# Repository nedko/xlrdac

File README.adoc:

[NOTE]
This is Work In Progress

Audio (XLR) Inputs and Outputs Open Source Hardware
project for use with libre software.

image:xlrdac-pcb-side.jpg["View of the line driver PCB", link="https://github.com/nedko/xlrdac/", width="100%"]

image:xlrdac-pcb.png["KiCAD screenshot of the line driver PCB", link="https://github.com/nedko/xlrdac/", width="100%"]

https://raw.githubusercontent.com/nedko/xlrdac/main/xlrdac-sch.pdf[Schematic], in PDF format.

Tools:

 * KiCAD - schematics and PCB design

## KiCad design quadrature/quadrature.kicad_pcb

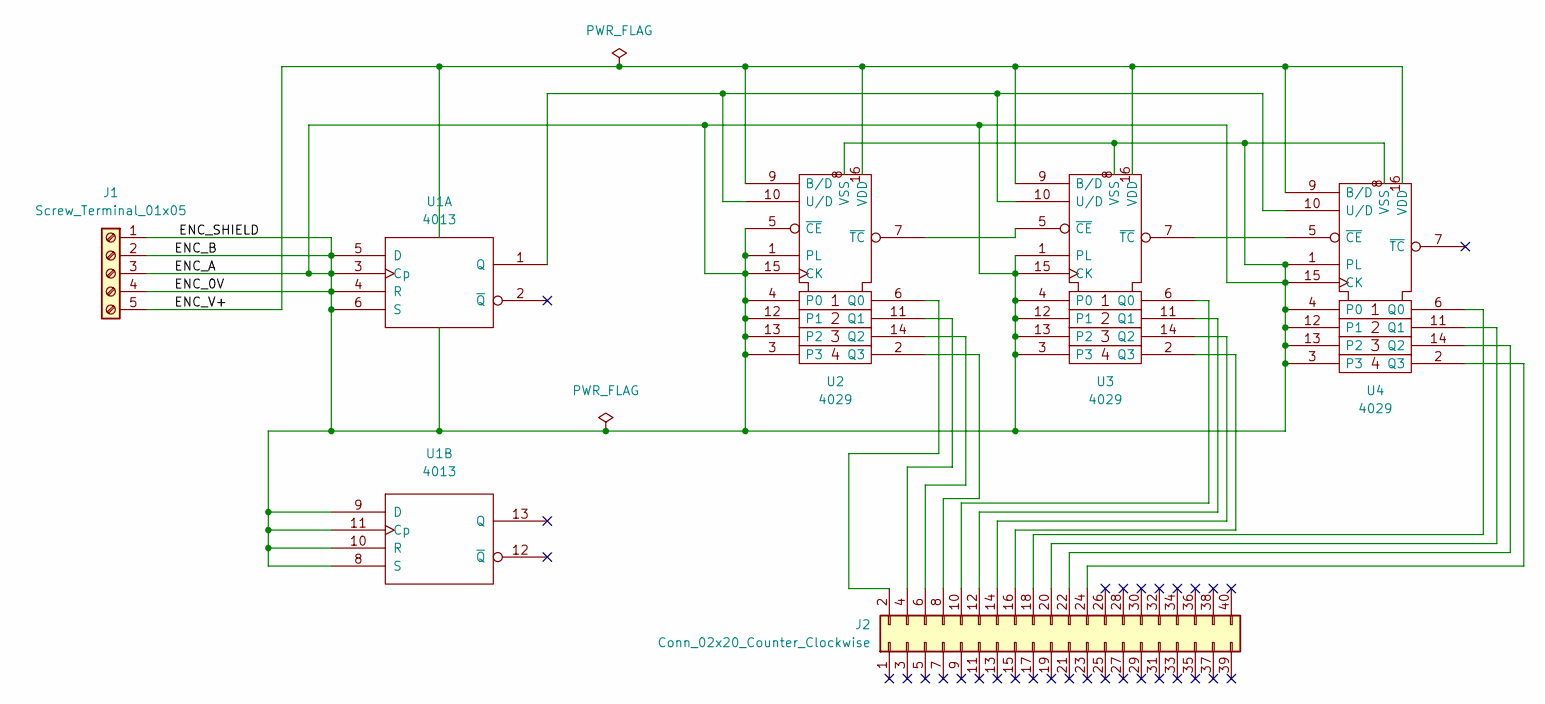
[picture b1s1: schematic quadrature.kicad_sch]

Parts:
J1: Screw_Terminal_01x05; TerminalBlock_bornier-5_P5.08mm
J2: Conn_02x20_Counter_Clockwise; IDC-Header_2x20_P2.54mm_Vertical
U1: 4013; DIP-14_W7.62mm_LongPads
U2, U3, U4: 4029; DIP-16_W7.62mm_LongPads

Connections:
unnamed: J2.2, U2.6 (Q0)
unnamed: J2.4, U2.11 (Q1)
unnamed: J2.6, U2.14 (Q2)
unnamed: J2.8, U2.2 (Q3)
unnamed: J2.10, U3.6 (Q0)
unnamed: J2.12, U3.11 (Q1)
unnamed: J2.14, U3.14 (Q2)
unnamed: J2.16, U3.2 (Q3)
unnamed: J2.18, U4.6 (Q0)
unnamed: J2.20, U4.11 (Q1)
unnamed: J2.22, U4.14 (Q2)
unnamed: J2.24, U4.2 (Q3)
unnamed: U1.1 (Q), U2.10 (U/D), U3.10 (U/D), U4.10 (U/D)
unnamed: U2.7 (~TC), U3.5 (~CE)
unnamed: U3.7 (~TC), U4.5 (~CE)
Vdd: J1.5, U1.14 (Vdd), U2.9 (B/D), U2.16 (VDD), U3.9 (B/D), U3.16 (VDD), U4.9 (B/D), U4.16 (VDD)
Vss: J1.1, J1.2, J1.3, J1.4, U1.3 (Cp), U1.4 (R), U1.5 (D), U1.6 (S), U1.7 (Vss), U1.8 (S), U1.9 (D), U1.10 (R), U1.11 (Cp), U2.1 (PL), U2.3, U2.4 (P0), U2.5 (~CE), U2.8 (VSS), U2.12 (P1), U2.13 (P2), U2.15 (CK), U3.1 (PL), U3.3, U3.4 (P0), U3.8 (VSS), U3.12 (P1), U3.13 (P2), U3.15 (CK), U4.1 (PL), U4.3, U4.4 (P0), U4.8 (VSS), U4.12 (P1), U4.13 (P2), U4.15 (CK)

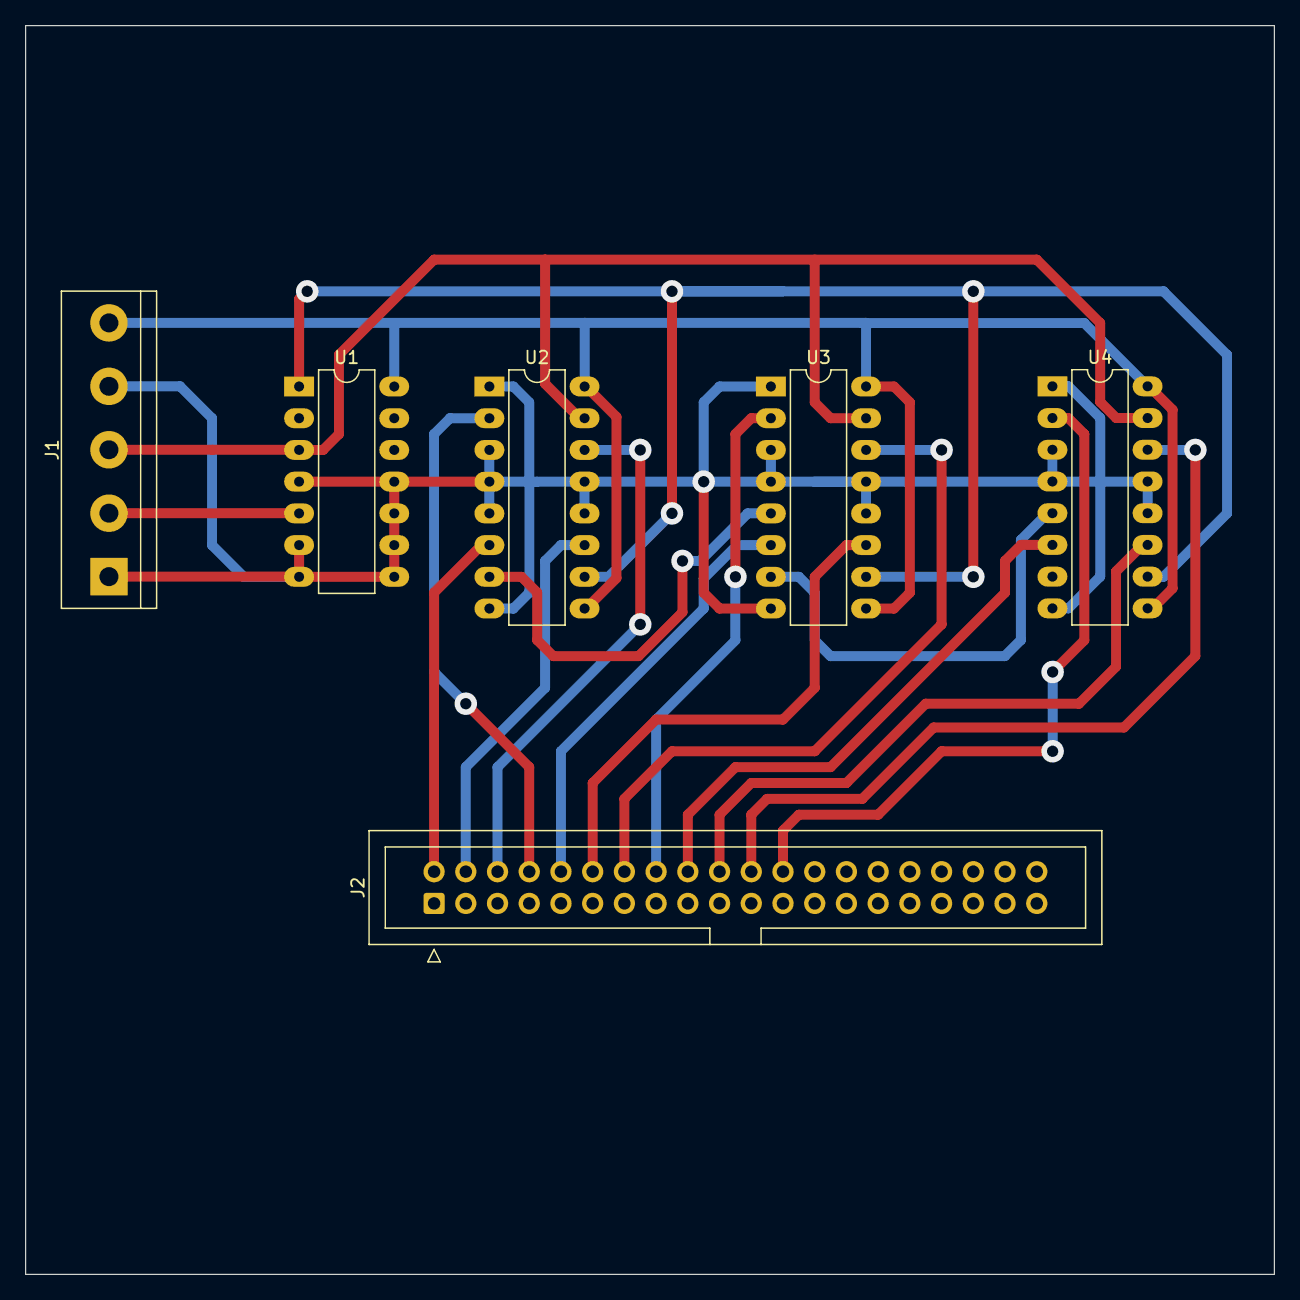
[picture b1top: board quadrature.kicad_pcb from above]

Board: 2 copper layers, 100.0 x 100.0 mm, 6 parts (0 on the bottom side), 17 nets.

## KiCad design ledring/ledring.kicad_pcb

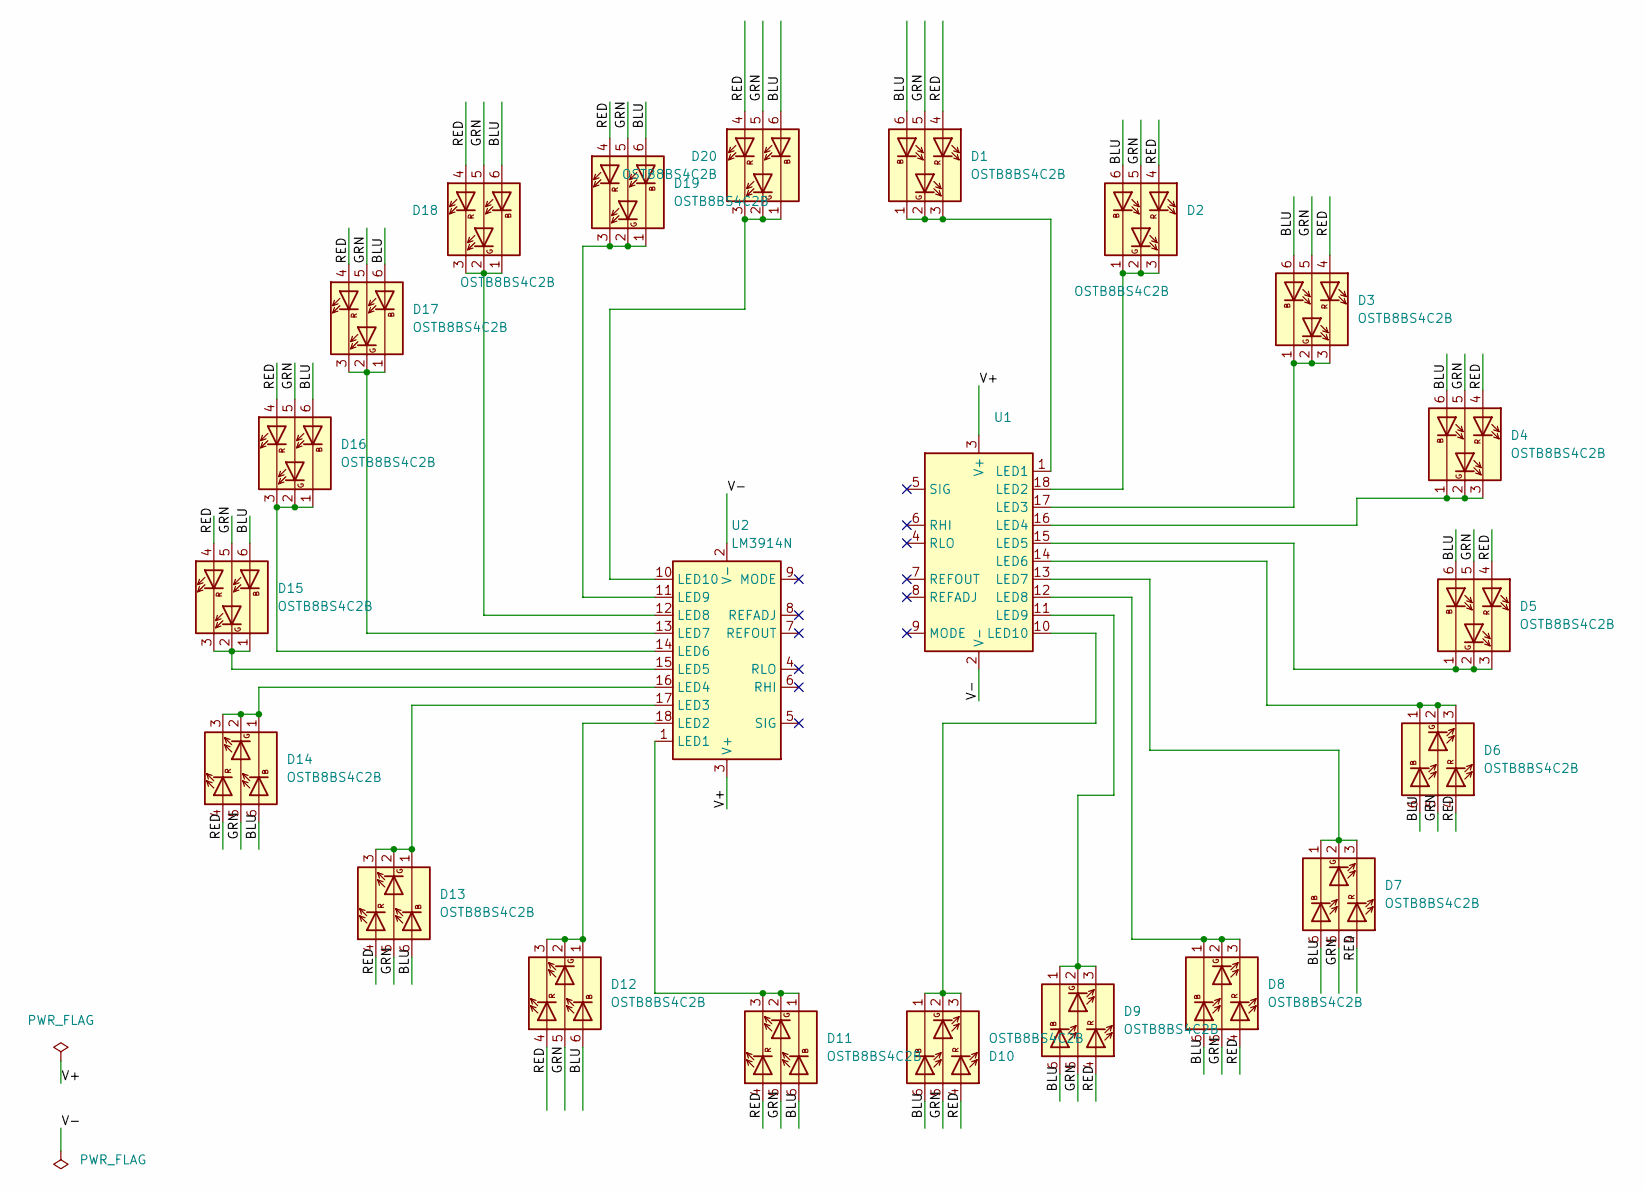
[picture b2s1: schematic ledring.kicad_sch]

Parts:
D1, D2, D3, D4, D5, D6, D7, D8, D9, D10, D11, D12, D13, D14, D15, D16, D17, D18, D19, D20: OSTB8BS4C2B; LED_Avago_PLCC6_3x2.8mm
U1: (no value)
U2: LM3914N; DIP-18_W7.62mm_LongPads

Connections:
/BLU: D1.6 (AB), D2.6 (AB), D3.6 (AB), D4.6 (AB), D5.6 (AB), D6.6 (AB), D7.6 (AB), D8.6 (AB), D9.6 (AB), D10.6 (AB), D11.6 (AB), D12.6 (AB), D13.6 (AB), D14.6 (AB), D15.6 (AB), D16.6 (AB), D17.6 (AB), D18.6 (AB), D19.6 (AB), D20.6 (AB)
/GRN: D1.5 (AG), D2.5 (AG), D3.5 (AG), D4.5 (AG), D5.5 (AG), D6.5 (AG), D7.5 (AG), D8.5 (AG), D9.5 (AG), D10.5 (AG), D11.5 (AG), D12.5 (AG), D13.5 (AG), D14.5 (AG), D15.5 (AG), D16.5 (AG), D17.5 (AG), D18.5 (AG), D19.5 (AG), D20.5 (AG)
/RED: D1.4 (AR), D2.4 (AR), D3.4 (AR), D4.4 (AR), D5.4 (AR), D6.4 (AR), D7.4 (AR), D8.4 (AR), D9.4 (AR), D10.4 (AR), D11.4 (AR), D12.4 (AR), D13.4 (AR), D14.4 (AR), D15.4 (AR), D16.4 (AR), D17.4 (AR), D18.4 (AR), D19.4 (AR), D20.4 (AR)
/V+: U1.3 (V+), U2.3 (V+)
/V-: U1.2 (V-), U2.2 (V-)
unnamed: D1.1 (KB), D1.2 (KG), D1.3 (KR), U1.1 (LED1)
unnamed: D2.1 (KB), D2.2 (KG), D2.3 (KR), U1.18 (LED2)
unnamed: D3.1 (KB), D3.2 (KG), D3.3 (KR), U1.17 (LED3)
unnamed: D4.1 (KB), D4.2 (KG), D4.3 (KR), U1.16 (LED4)
unnamed: D5.1 (KB), D5.2 (KG), D5.3 (KR), U1.15 (LED5)
unnamed: D6.1 (KB), D6.2 (KG), D6.3 (KR), U1.14 (LED6)
unnamed: D7.1 (KB), D7.2 (KG), D7.3 (KR), U1.13 (LED7)
unnamed: D8.1 (KB), D8.2 (KG), D8.3 (KR), U1.12 (LED8)
unnamed: D9.1 (KB), D9.2 (KG), D9.3 (KR), U1.11 (LED9)
unnamed: D10.1 (KB), D10.2 (KG), D10.3 (KR), U1.10 (LED10)
unnamed: D11.1 (KB), D11.2 (KG), D11.3 (KR), U2.1 (LED1)
unnamed: D12.1 (KB), D12.2 (KG), D12.3 (KR), U2.18 (LED2)
unnamed: D13.1 (KB), D13.2 (KG), D13.3 (KR), U2.17 (LED3)
unnamed: D14.1 (KB), D14.2 (KG), D14.3 (KR), U2.16 (LED4)
unnamed: D15.1 (KB), D15.2 (KG), D15.3 (KR), U2.15 (LED5)
unnamed: D16.1 (KB), D16.2 (KG), D16.3 (KR), U2.14 (LED6)
unnamed: D17.1 (KB), D17.2 (KG), D17.3 (KR), U2.13 (LED7)
unnamed: D18.1 (KB), D18.2 (KG), D18.3 (KR), U2.12 (LED8)
unnamed: D19.1 (KB), D19.2 (KG), D19.3 (KR), U2.11 (LED9)
unnamed: D20.1 (KB), D20.2 (KG), D20.3 (KR), U2.10 (LED10)

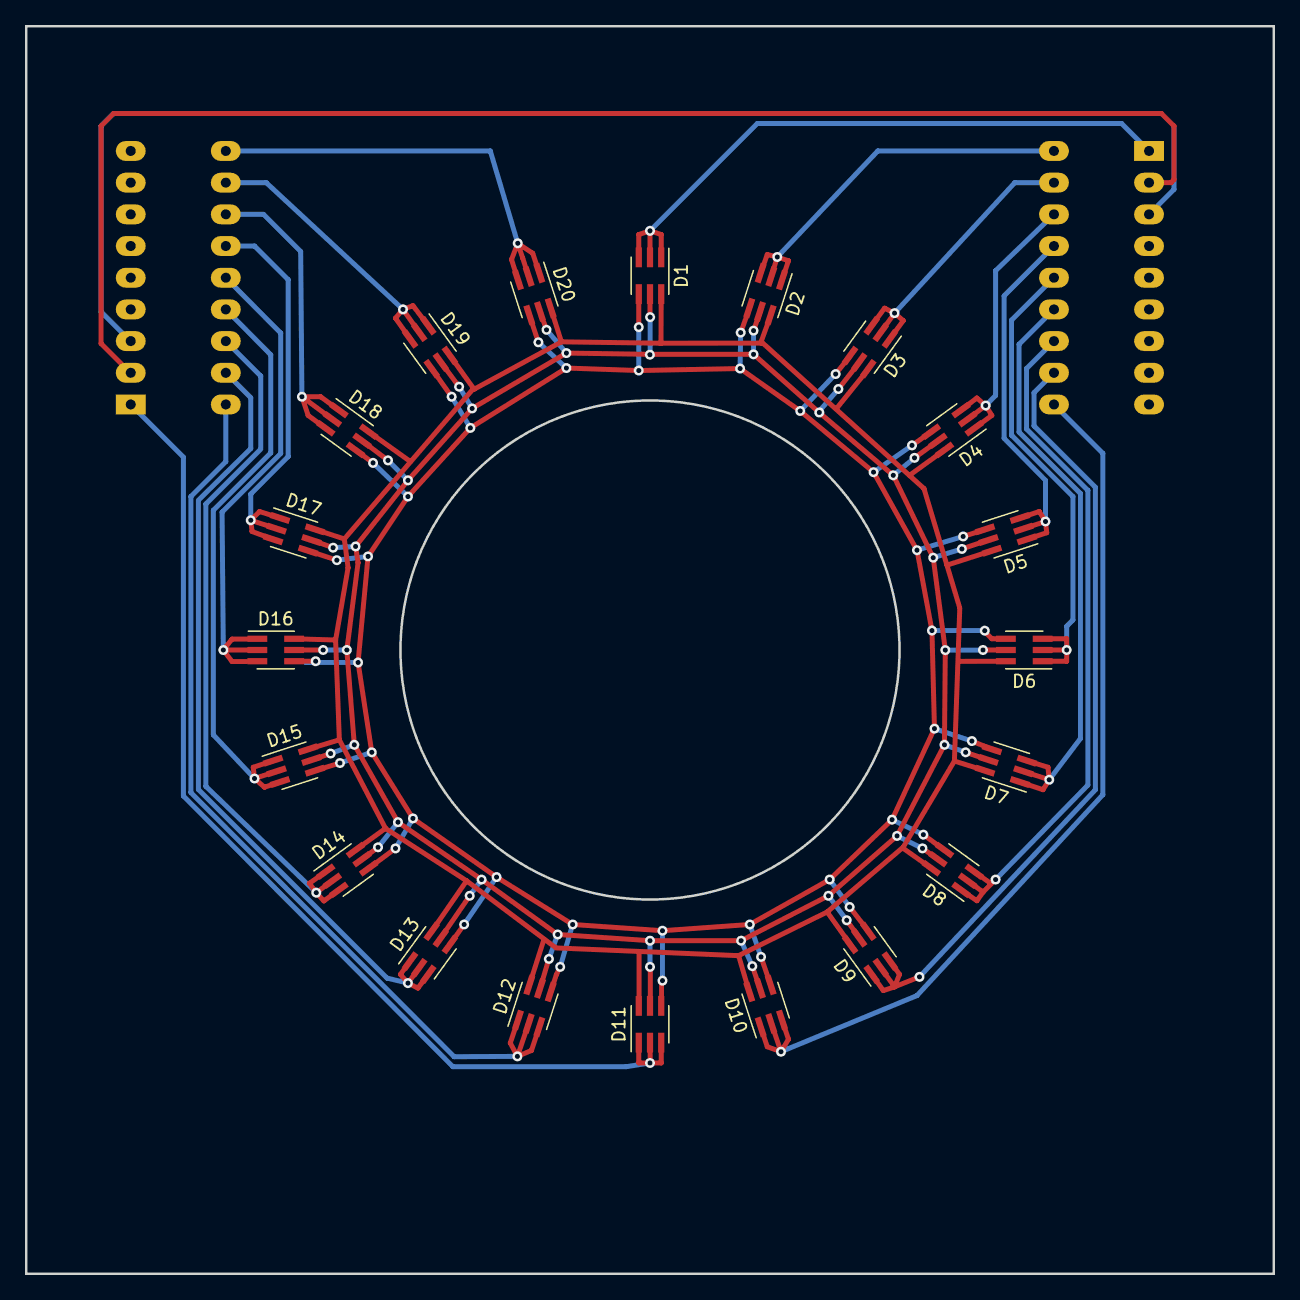
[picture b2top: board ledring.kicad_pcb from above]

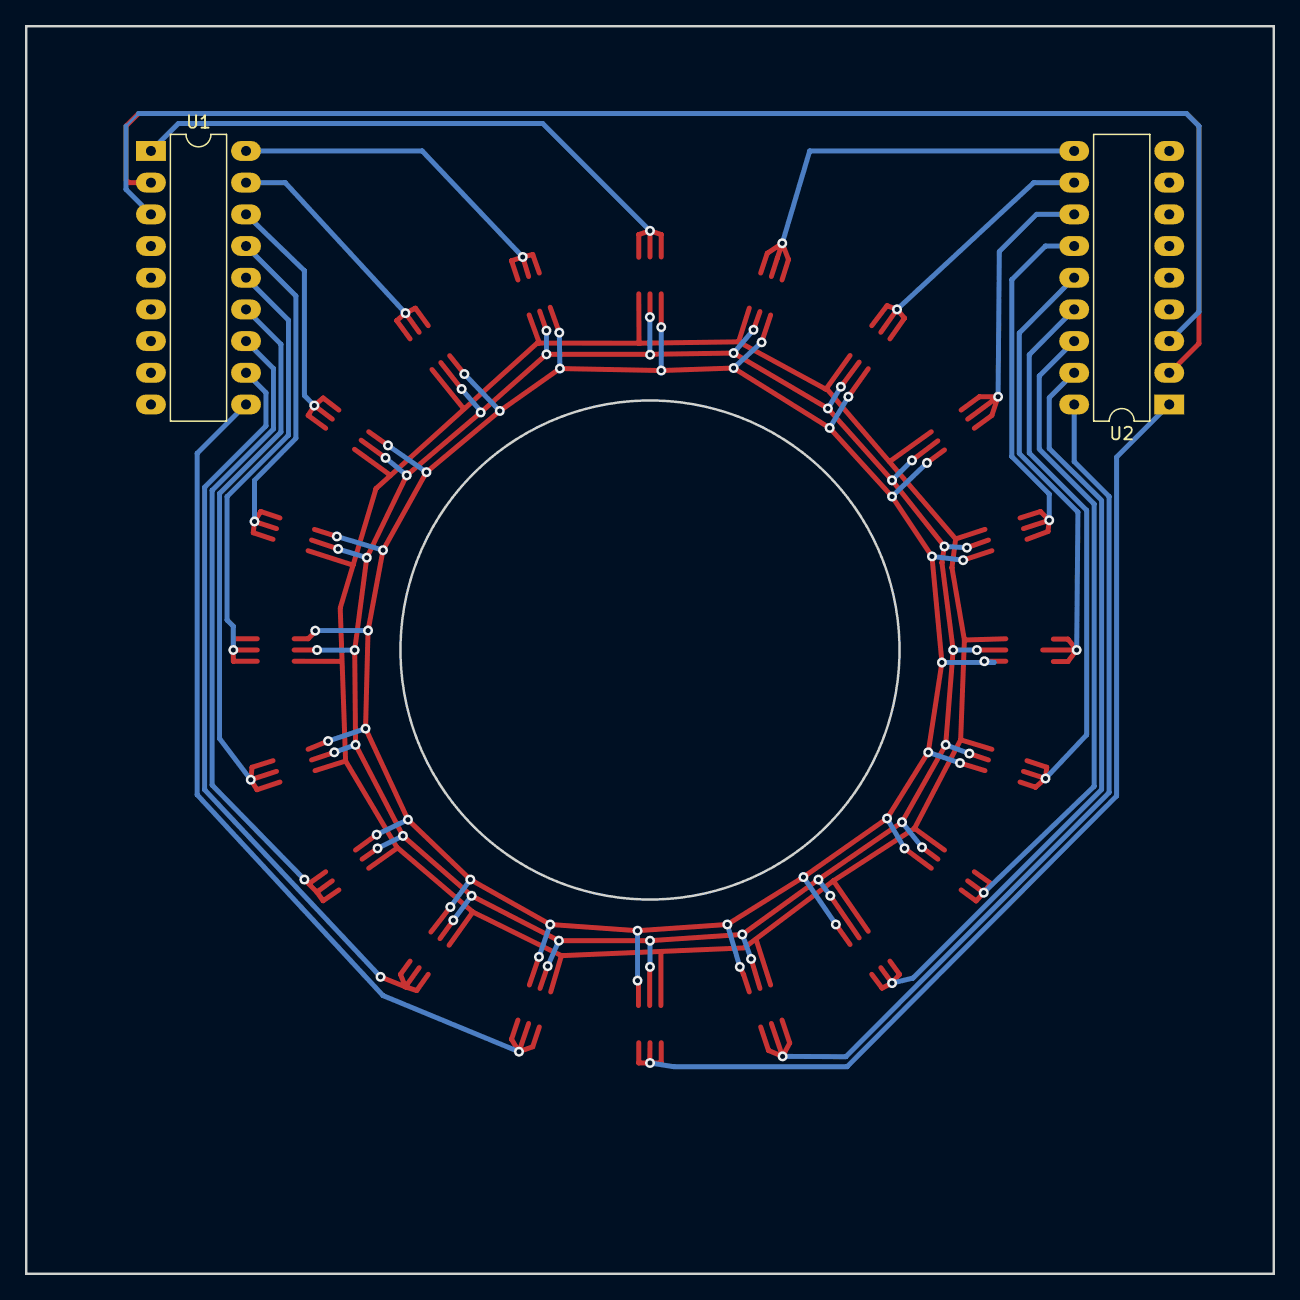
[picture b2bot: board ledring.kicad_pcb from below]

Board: 2 copper layers, 100.0 x 100.0 mm, 22 parts (2 on the bottom side), 25 nets.

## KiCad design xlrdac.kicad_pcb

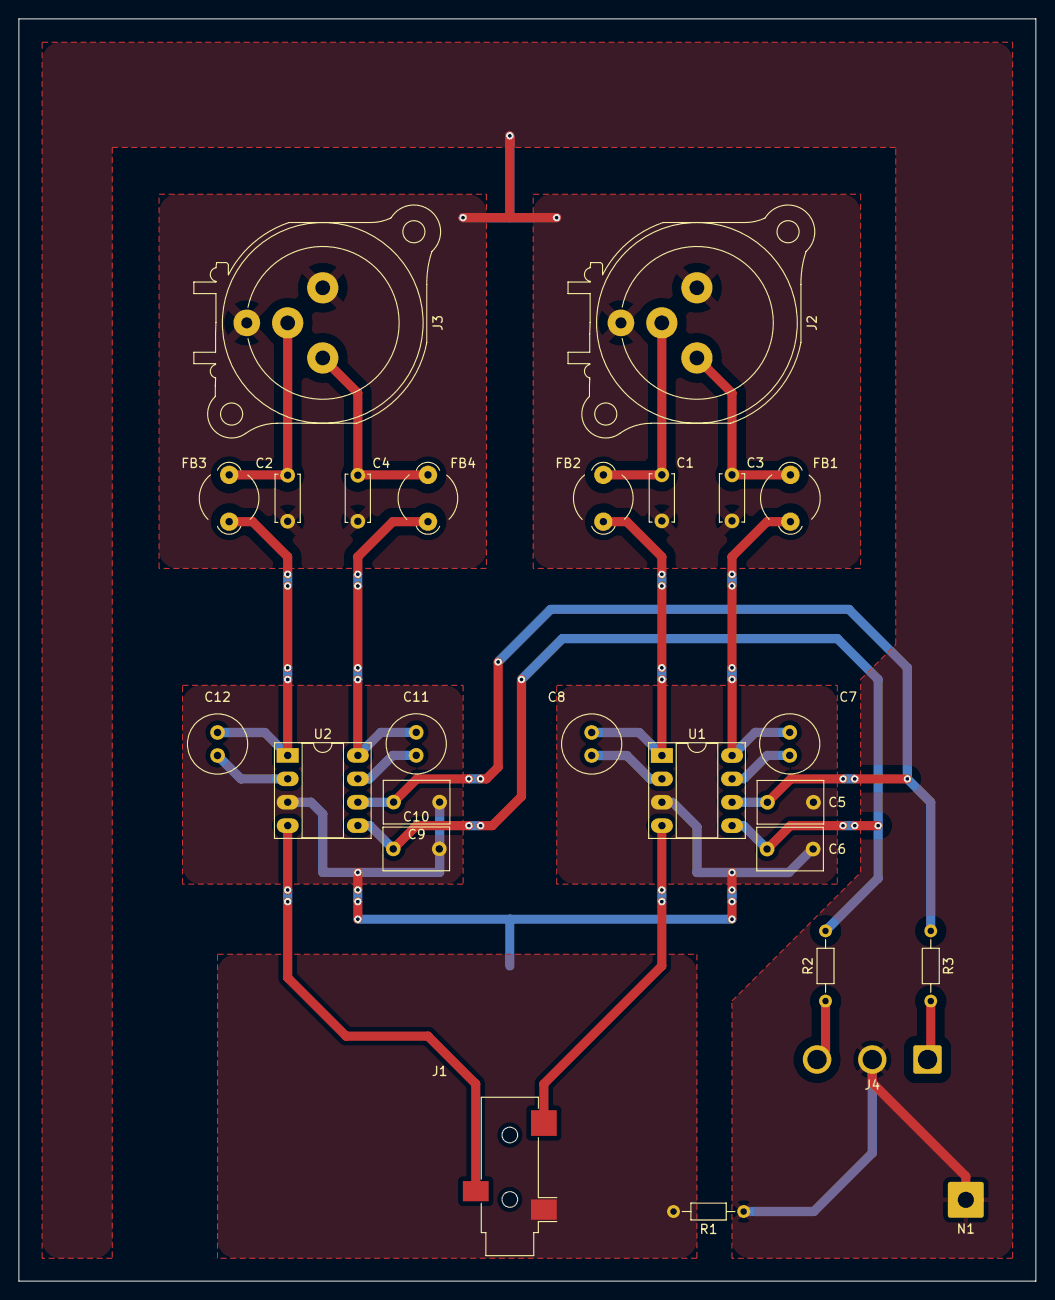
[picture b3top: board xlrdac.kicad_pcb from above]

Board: 2 copper layers, 110.5 x 137.1 mm, 26 parts (0 on the bottom side), 20 nets.

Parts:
C1, C2, C3, C4: 100pF; C_Disc_D5.0mm_W2.5mm_P5.00mm
C5, C6, C9, C10: 100nF; C_Rect_L7.0mm_W4.5mm_P5.00mm
C7, C8, C11, C12: 10uF NP; C_Radial_D6.3mm_H11.0mm_P2.50mm
FB1, FB2, FB3, FB4: RF choke; LairdTech_28C0236-0JW-10
J1: StereoIn; Jack_3.5mm_CUI_SJ-3523-SMT_Horizontal
J2: Left Output; Jack_XLR_Neutrik_NC3MAV_Vertical
J3: Right Output; Jack_XLR_Neutrik_NC3MAV_Vertical
J4: PWR ENTRY; SolderWire-1.5sqmm_1x03_P6mm_D1.7mm_OD3mm
N1: CASE SHIELD; SolderWire-1sqmm_1x01_D1.4mm_OD3.9mm
R1, R2, R3: 0R; R_Axial_DIN0204_L3.6mm_D1.6mm_P7.62mm_Horizontal
U1, U2: THAT1646; DIP-8_W7.62mm_Socket_LongPads

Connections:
/Line Driver Left/IN: J1.T, U1.4 (IN1)
/Line Driver Left/OUT+: C7.2, FB1.1, U1.8 (OUT+)
/Line Driver Left/OUT-: C8.2, FB2.1, U1.1 (OUT-)
/Line Driver Right/IN: J1.R, U2.4 (IN1)
/Line Driver Right/OUT+: C11.2, FB4.1, U2.8 (OUT+)
/Line Driver Right/OUT-: C12.2, FB3.1, U2.1 (OUT-)
GNDA: C5.1, C6.2, C9.1, C10.2, J1.S, R1.2, U1.3 (GND), U2.3 (GND)
unnamed: C1.1, FB2.2, J2.3
unnamed: C2.2, FB3.2, J3.3
unnamed: C3.1, FB1.2, J2.2
unnamed: C4.2, FB4.2, J3.2
unnamed: C7.1, U1.7 (SNS+)
unnamed: C8.1, U1.2 (SNS-)
unnamed: C11.1, U2.7 (SNS+)
unnamed: C12.1, U2.2 (SNS-)
PWR.GND: C1.2, C2.1, C3.2, C4.1, J2.1, J2.G, J3.1, J3.G, J4.2, N1.1 (PAD), R1.1
PWR.VCC: J4.1, R3.2
PWR.VEE: J4.3, R2.1
VCC: C5.2, C9.2, R3.1, U1.6 (V+), U2.6 (V+)
VEE: C6.1, C10.1, R2.2, U1.5 (V-), U2.5 (V-)

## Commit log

2022-10-07 Initial version of XLR line drivers
2022-10-07 PDF render for schematic, raster render for PCB
2022-10-07 gitignore cache and local backups
2022-10-07 Add README.adoc
2022-10-07 README.adoc: Fix syntax
2022-10-07 README.adoc: Add a PCB view
2022-10-07 Add rendered README.html
    asciidoc -b html5 -a data-uri -a icons --theme ladi README.adoc
    asciidoc is from https://github.com/LADI/ladoc-py
2022-10-07 README.adoc: Add link to gh
2022-10-07 Remove README.html
2022-10-09 README.adoc: Add link to schematic PDF
2022-10-09 Rework grounding, export side view
2022-10-09 xlrdac-sch.pdf: Update from source
2022-10-09 Improve ground planes
2022-10-09 Screenshot from KiCAD's PCB editor
2022-10-09 pcb: Remove PCBWay Project ID and put gh url instead
2022-10-09 pcb: Disable high contrast mode
2022-10-09 README.adoc: Add KiCAD PCB screenshot
2022-10-18 Move line drivers to dedicated file
2022-10-18 Regenerate jpeg&pdf files; png->jpeg
2022-10-18 Rework GNDA around stereo in
2022-11-01 Initial version of the front panel
    Diecast Enclosure 26357PSLA from hammfg.com
    is used as basis
2022-11-02 Improve drilling
2022-11-02 git-ignore *.FCStd1
    These are FreeCAD backup files
2022-11-02 Fix drilling
2022-11-02 Split drilling sketches
2022-11-02 LED ring drills
2022-11-04 Initial version of the LED ring around rotary encoder
2022-11-04 Increase ledring diameter to 70mm; LED driling sketch
2022-11-05 ledring: Adjust PCB routing (angles)
2022-11-05 Add ledring-pcb png
2022-11-08 ledring: switch from LM3914V (PLCC-20) to LM3914N (DIP-18)
2022-11-08 Exact radial placement of LEDs
2022-11-08 ledring: update routing
2022-11-09 Initial version of quadrature decoder (of rotary encoder)
2022-11-10 Improve routing
2022-11-10 Use ledring and quadrature from the subprojects
